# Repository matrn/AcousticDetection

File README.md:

# System for Acoustic Detection and Localization Based on Two Microphones
# Systém pro akustickou detekci a lokalizaci založený na dvou mikrofonech

This repository contains the source code, schematic, and PCB layout of a demonstration device designed to detect and locate acoustic impulse events. The device is composed of an ESP32 microcontroller and two MEMS microphones SPH0645LM4H.

## Directories
- `AcousticDetection_HW/` - KiCad schematic & PCB
- `AcousticDetection_SW/` - source code of the ESP32 firmware
- `web` - source code for the ESP32 web page
- `models` - 3D models for 3D printing
- `dsp_toolbox/` - some tools used during development of the signal processing

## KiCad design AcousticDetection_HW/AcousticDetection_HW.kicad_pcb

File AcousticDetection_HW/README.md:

# KiCad schematic and PCB layout of the AcousticDetection device

## Directories
- `lib/` - additional KiCad libraries used for the PCB
- `gerber/` - gerber export ready for production, it containes `single/` version where all three parts are in the same file and `separated/` for three separated gerber files
- `FORMODEL-AcousticDetection_HW/` - copy of this main `AcousticDetection_HW` PCB files, used for the images export into final thesis. Do not use this for production.
- `plots/` - PDF plots of schematic & PCB layout

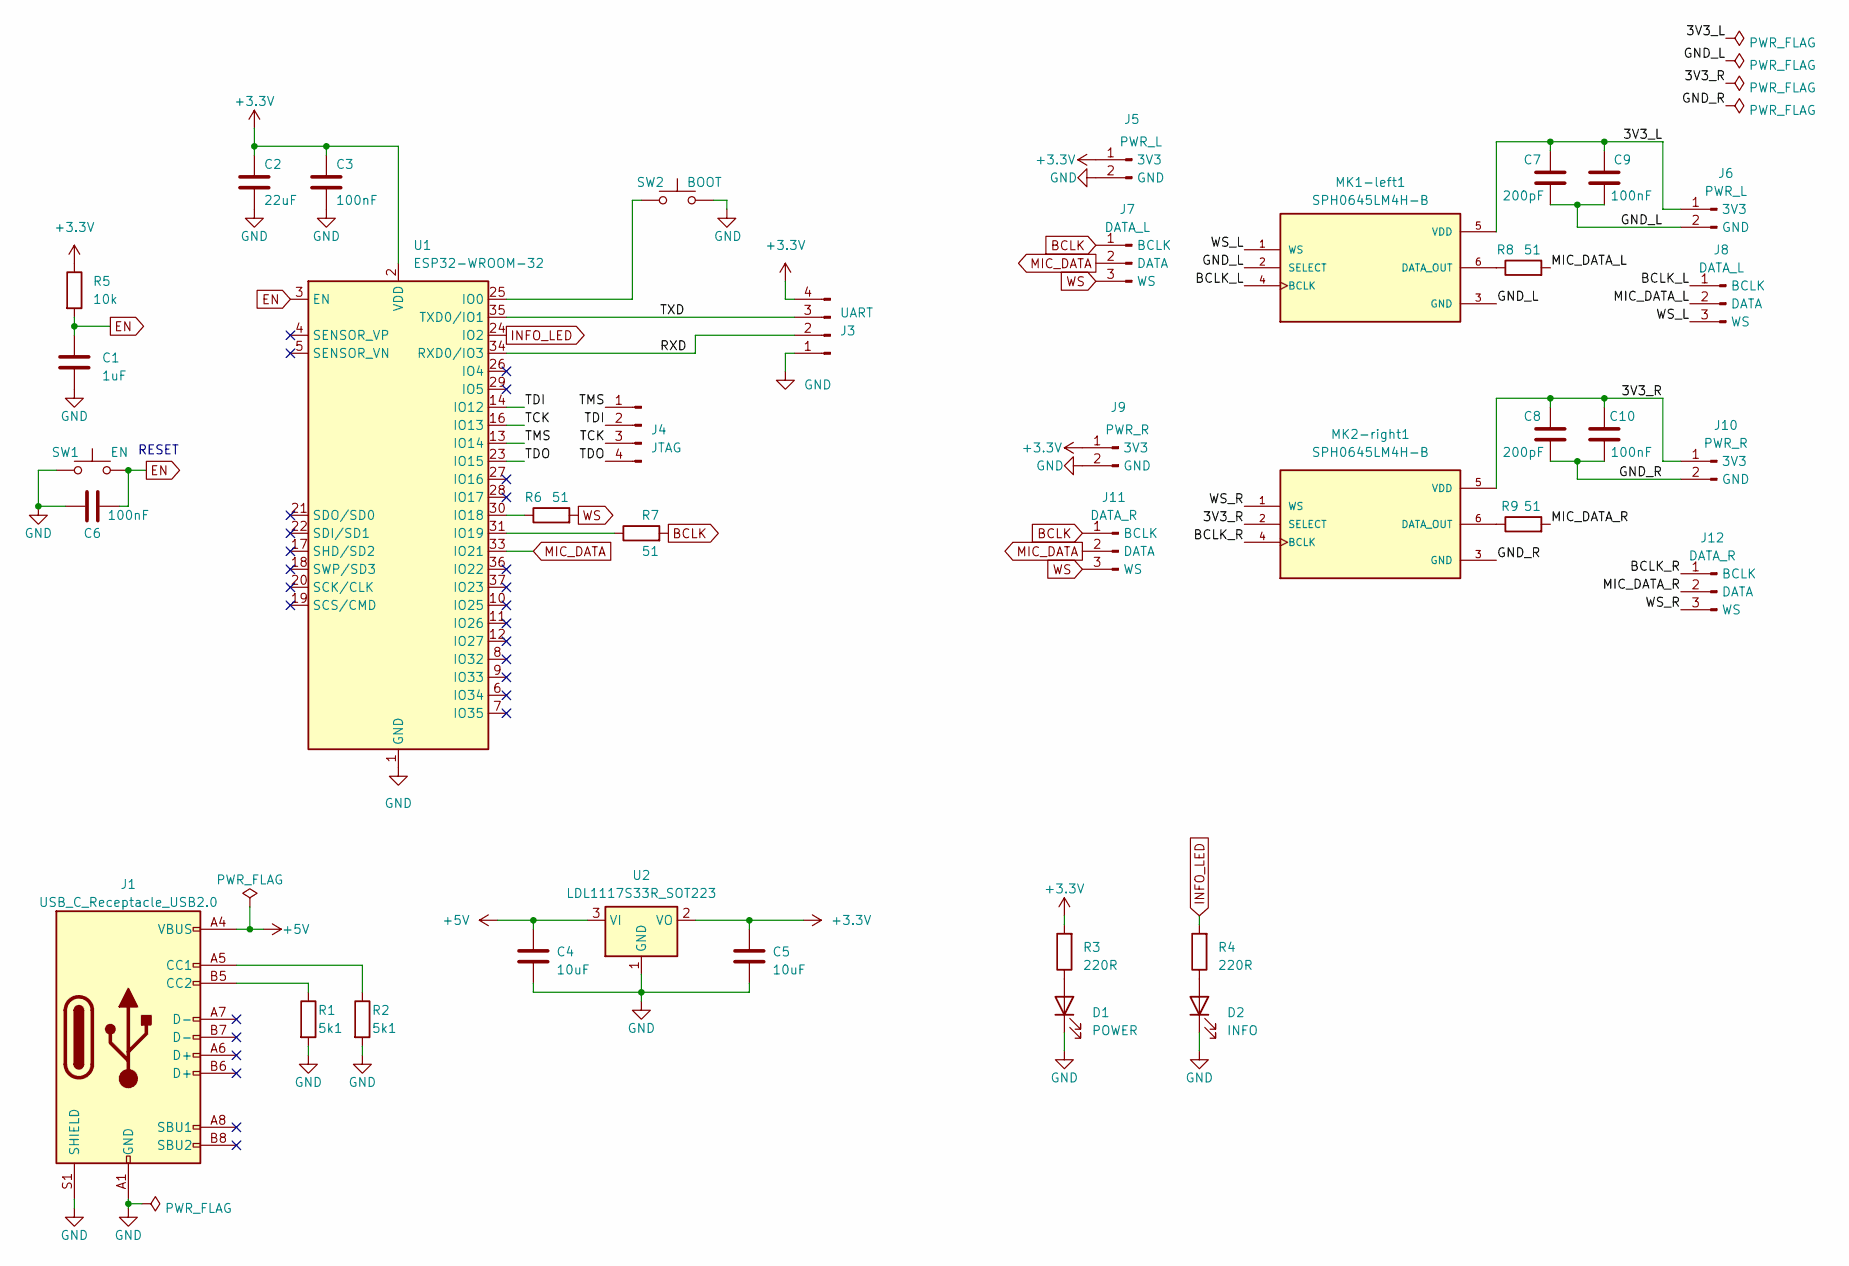
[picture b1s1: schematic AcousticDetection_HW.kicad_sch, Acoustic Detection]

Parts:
C1: 1uF; C_0805_2012Metric_Pad1.18x1.45mm_HandSolder
C2: 22uF; C_1206_3216Metric_Pad1.33x1.80mm_HandSolder
C3, C6: 100nF; C_0805_2012Metric_Pad1.18x1.45mm_HandSolder
C4, C5: 10uF; C_1206_3216Metric_Pad1.33x1.80mm_HandSolder
C7, C8: 200pF; C_0603_1608Metric_Pad1.08x0.95mm_HandSolder
C9, C10: 100nF; C_0603_1608Metric_Pad1.08x0.95mm_HandSolder
D1: POWER; LED_1206_3216Metric_Pad1.42x1.75mm_HandSolder
D2: INFO; LED_1206_3216Metric_Pad1.42x1.75mm_HandSolder
J1: USB_C_Receptacle_USB2.0; USB_C_Receptacle_GCT_USB4105-xx-A_16P_TopMnt_Horizontal
J3: UART; PinHeader_1x04_P2.54mm_Vertical
J4: JTAG; PinHeader_1x04_P2.54mm_Vertical
J5, J6: PWR_L; PowerConnector
J7, J8: DATA_L; DataConnector
J9, J10: PWR_R; PowerConnector
J11, J12: DATA_R; DataConnector
MK1-left1, MK2-right1: SPH0645LM4H-B; MIC_SPH0645LM4H-B
R1, R2: 5k1; R_0805_2012Metric_Pad1.20x1.40mm_HandSolder
R3, R4: 220R; R_0805_2012Metric_Pad1.20x1.40mm_HandSolder
R5: 10k; R_0805_2012Metric_Pad1.20x1.40mm_HandSolder
R6, R7: 51; R_0805_2012Metric_Pad1.20x1.40mm_HandSolder
R8, R9: 51; R_0603_1608Metric_Pad0.98x0.95mm_HandSolder
SW1: EN; SW_Tactile_SPST_NO_Straight_CK_PTS636Sx25SMTRLFS
SW2: BOOT; SW_Tactile_SPST_NO_Straight_CK_PTS636Sx25SMTRLFS
U1: ESP32-WROOM-32
U2: LDL1117S33R_SOT223; SOT-223-3_TabPin2

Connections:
+3.3V: C2.2, C3.2, C5.1, J3.4, J5.1 (3V3), J9.1 (3V3), R3.2, R5.1, U1.2 (VDD), U2.2 (VO)
+5V: C4.1, J1.A4 (VBUS), J1.A9 (VBUS), J1.B4 (VBUS), J1.B9 (VBUS), U2.3 (VI)
/3V3_L: C7.2, C9.2, J6.1 (3V3), MK1-left1.5 (VDD)
/3V3_R: C8.2, C10.2, J10.1 (3V3), MK2-right1.2 (SELECT), MK2-right1.5 (VDD)
/BCLK_L: J8.1 (BCLK), MK1-left1.4 (BCLK)
/BCLK_R: J12.1 (BCLK), MK2-right1.4 (BCLK)
/GND_L: C7.1, C9.1, J6.2 (GND), MK1-left1.2 (SELECT), MK1-left1.3 (GND)
/GND_R: C8.1, C10.1, J10.2 (GND), MK2-right1.3 (GND)
/MIC_DATA_L: J8.2 (DATA), R8.2
/MIC_DATA_R: J12.2 (DATA), R9.2
/RXD: J3.2, U1.34 (RXD0/IO3)
/TCK: J4.3, U1.16 (IO13)
/TDI: J4.2, U1.14 (IO12)
/TDO: J4.4, U1.23 (IO15)
/TMS: J4.1, U1.13 (IO14)
/TXD: J3.3, U1.35 (TXD0/IO1)
/WS_L: J8.3 (WS), MK1-left1.1 (WS)
/WS_R: J12.3 (WS), MK2-right1.1 (WS)
BCLK: J7.1 (BCLK), J11.1 (BCLK), R7.2
EN: C1.2, C6.2, R5.2, SW1.2, U1.3 (EN)
GND: C1.1, C2.1, C3.1, C4.2, C5.2, C6.1, D1.1 (K), D2.1 (K), J1.A1 (GND), J1.A12 (GND), J1.B1 (GND), J1.B12 (GND), J1.S1 (SHIELD), J3.1, J5.2 (GND), J9.2 (GND), R1.2, R2.2, SW1.1, SW2.2, U1.1 (GND), U1.15 (GND), U1.38 (GND), U1.39 (GND), U2.1 (GND)
INFO_LED: R4.2, U1.24 (IO2)
MIC_DATA: J7.2 (DATA), J11.2 (DATA), U1.33 (IO21)
unnamed: D1.2 (A), R3.1
unnamed: D2.2 (A), R4.1
unnamed: J1.A5 (CC1), R2.1
unnamed: J1.B5 (CC2), R1.1
unnamed: MK1-left1.6 (DATA_OUT), R8.1
unnamed: MK2-right1.6 (DATA_OUT), R9.1
unnamed: SW2.1, U1.25 (IO0)
unnamed: R6.1, U1.30 (IO18)
unnamed: R7.1, U1.31 (IO19)
WS: J7.3 (WS), J11.3 (WS), R6.2

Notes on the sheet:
RESET

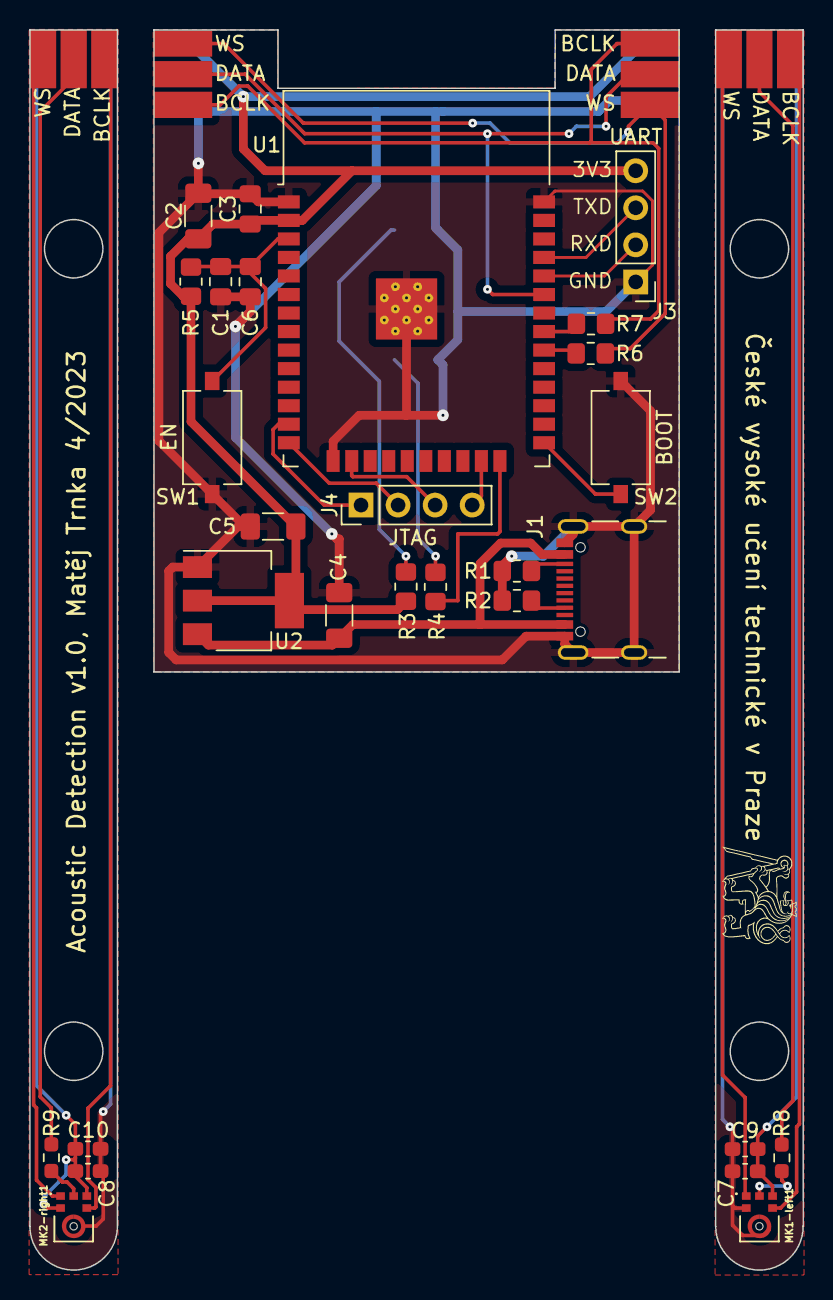
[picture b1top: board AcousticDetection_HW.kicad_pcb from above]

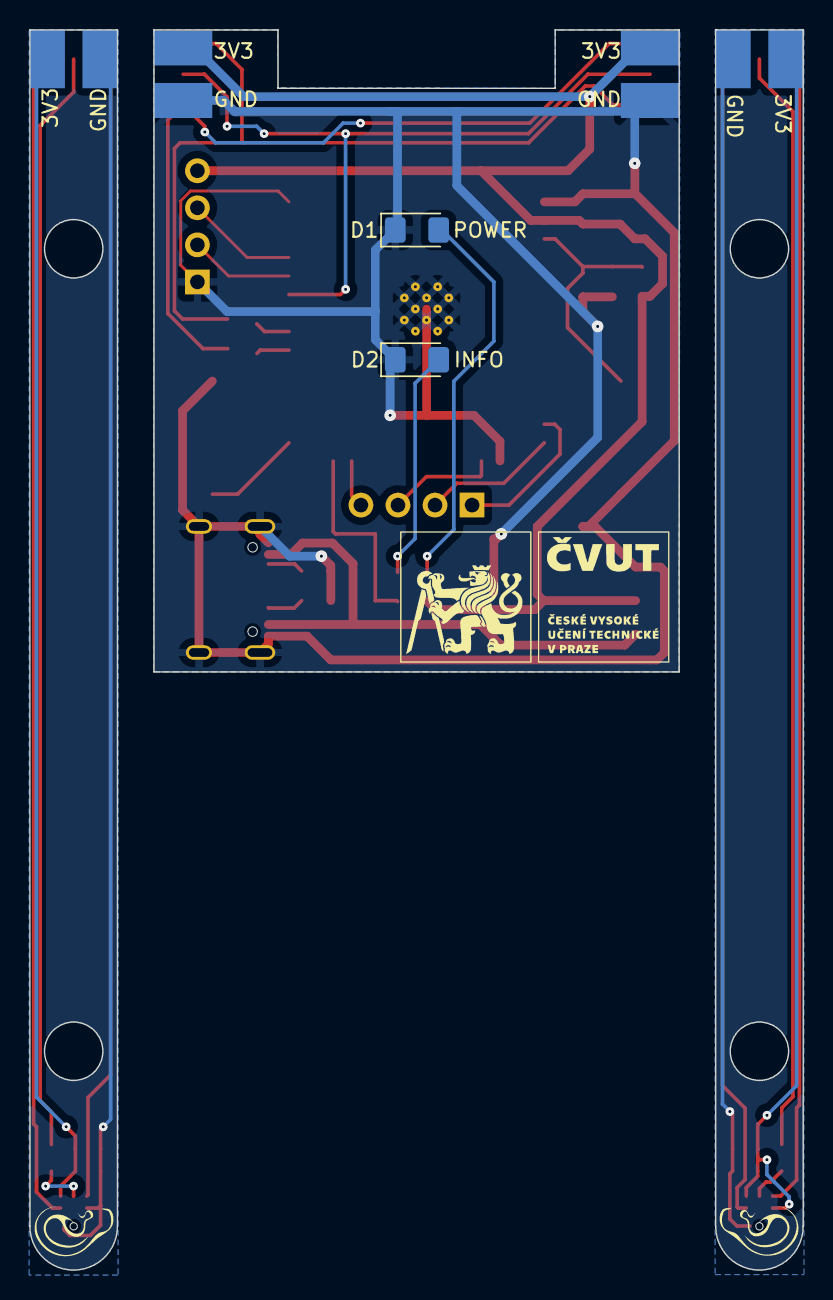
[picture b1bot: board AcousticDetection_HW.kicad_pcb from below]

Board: 2 copper layers, 53.0 x 85.0 mm, 38 parts (6 on the bottom side), 33 nets.

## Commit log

2022-10-15 initial work
2022-10-27 working on schematic
2022-11-05 add i2s mems microphones reading
2022-11-05 add DC filter & testing correlation of signals
2022-11-06 working on web interface
2022-11-14 working on signal processing
2022-11-16 working on DSP debug toolbox
2022-11-27 debugging dsp
2022-11-27 working on getting i2s mics sampling done
2022-11-28 add tools for streaming mics audio into web server
2022-12-21 fix cross correlation & add debug of it
2023-01-22 before change from .csv to .raw format
2023-01-22 add avg (for moving average)
2023-01-22 sampler changed to .raw file support
2023-01-22 add var
2023-01-22 used bigger integer to avoid overflow in xcorr & add abs to xcorr compare
2023-01-22 algorithm update
2023-01-22 DSP toolbox - improving charts, testing onset detection
2023-01-22 canvas web interface updates
2023-01-22 add plotly web interface
2023-01-22 web appearence updates
2023-01-22 add cross correlation max_time check
2023-01-29 add index page for ESP web server
2023-03-16 add 3D model of case for prototype
2023-03-16 polar chart is rotated
2023-03-17 refactoring
2023-03-18 refactoring of Web Interface & add SSE
2023-03-18 add purgecss for bootstrap
2023-03-18 add bundling scripts for statics files to minimize size
2023-03-18 add SPIFFS preaction to bundle static files
2023-03-18 add docs & flush=True for print
2023-03-19 add OTA support
2023-03-19 add 100ms delay for onset detector
2023-03-19 add alive timer for SSE
2023-03-19 add chart height auto resize
2023-03-19 add debug, release & debug-OTA envs
2023-03-19 added WiFi QR code generator
2023-03-19 add url QR generator
2023-03-19 add WiFi AP with DNS redirect
2023-03-19 add plotly.js custom bundle
2023-03-19 fix typo
2023-03-19 matlab dsp debug scripts
2023-03-20 add wifi AP channel into config
2023-04-05 schematic update
2023-04-09 add connection pads
2023-04-09 small fixes
2023-04-09 working on pcb layout
2023-04-11 add POWER symbol for ERC & add parts links
2023-04-11 fix pin types in symbols for ERC
2023-04-16 finishing pcb
2023-04-16 cleanup
2023-04-17 small changes
2023-04-17 parts labels reposition
2023-04-18 pcb fabrication
2023-04-18 add separated parts
2023-04-18 all parts on a single board
2023-05-08 the resistor values of pcb leds were changed to 220R
2023-05-08 add comments
2023-05-21 add version for 3D export and models
2023-05-21 add title
2023-05-21 schematic cleanup
2023-05-21 add schematic plot
2023-05-21 add pcb pdf export
2023-05-23 updating web server default settings
2023-05-23 fix platformio OTA upload
2023-05-23 changed mics distance to 0.2m (new board)
2023-05-23 add angle error & variable barpolar width into UI
2023-05-23 add quadratic interpolation
2023-05-23 add quadratic interpolation result check
2023-05-23 fix mistake in quadratic interpolation formula
2023-05-25 add README
2023-05-25 add comments & code format
2023-05-25 add example of the config.hpp
2023-05-25 removing unused code
2023-05-25 fix test
2023-05-25 add comments & code formatting
2023-05-25 code formatting
2023-05-25 README updates
2023-05-25 add web interface image
2023-05-25 Create LICENSE
2023-06-12 add case for the final device
2023-07-15 changed arms screw holders outer diameter & add usb-c soldering holes
2023-07-17 case improvements
2023-07-17 add gitignore
2023-07-31 enable wifi ap by default
2024-01-08 add release-ota
2024-01-08 add threshold settings method for OnsetDetector
2024-01-08 add OnsetDetector threshold update via POST request & saving to EEPROM
2024-01-09 add missing EEPROM.commit()
